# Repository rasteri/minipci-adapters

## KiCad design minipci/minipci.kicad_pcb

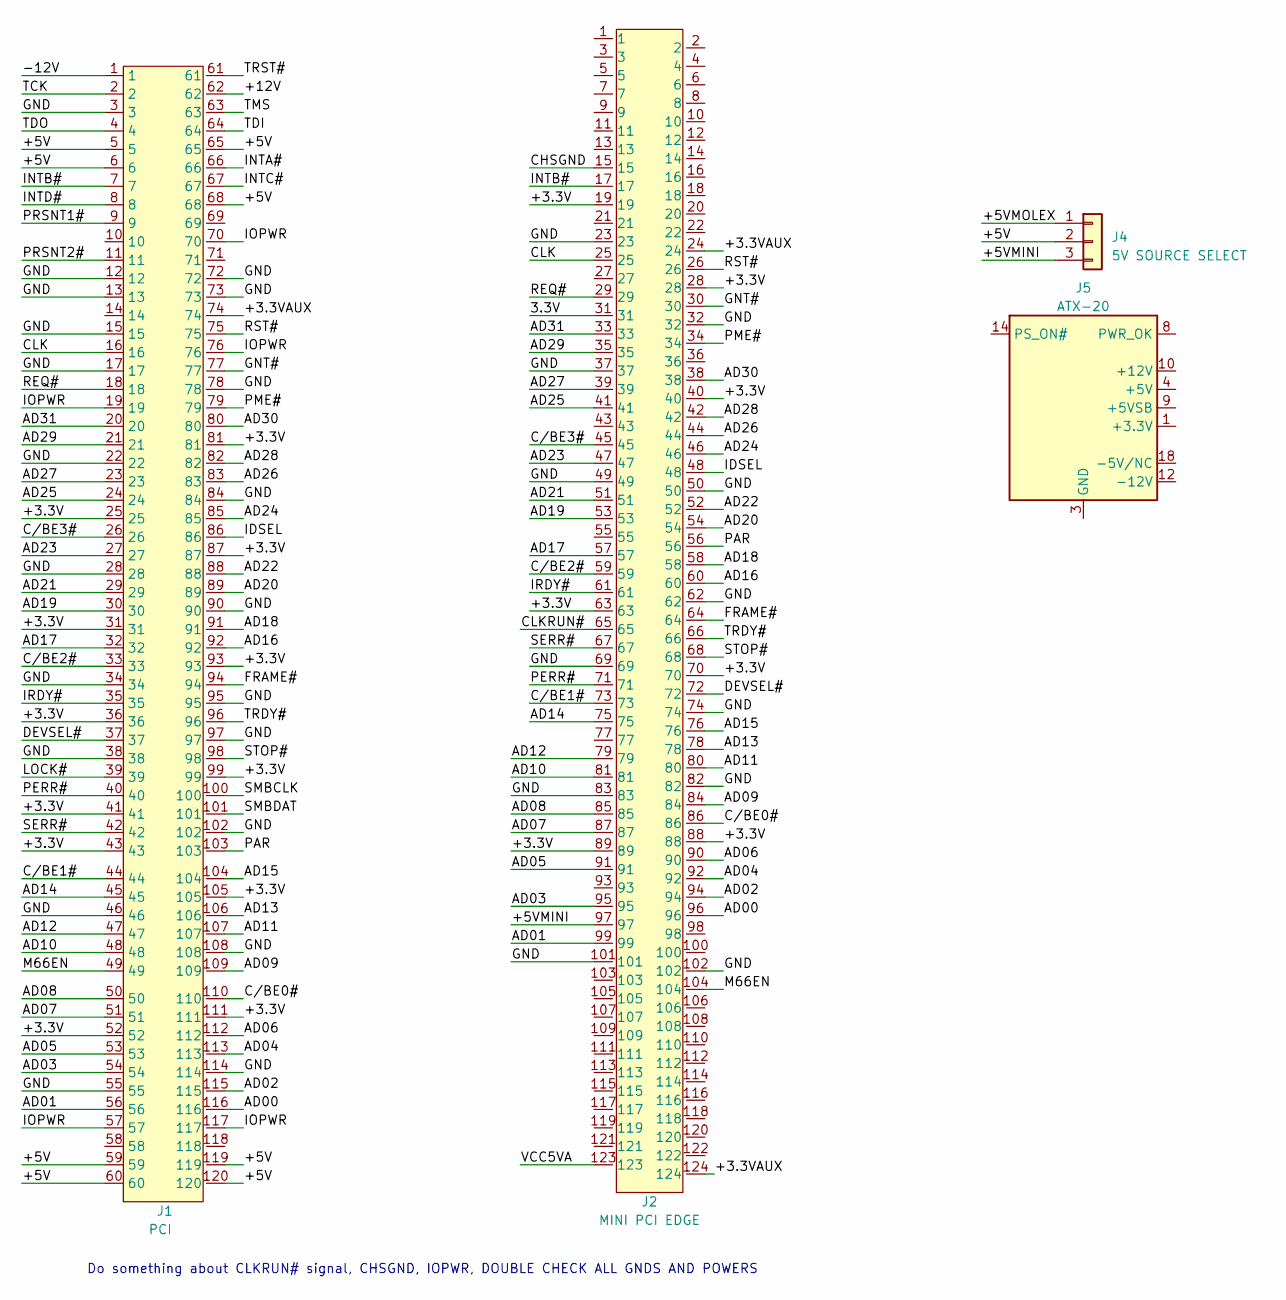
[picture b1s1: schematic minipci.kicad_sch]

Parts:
J1: PCI; 5145154-1
J2: MINI PCI EDGE; minipci
J4: 5V SOURCE SELECT; PinHeader_1x03_P2.54mm_Vertical
J5: ATX-20; Molex_Mini-Fit_Jr_5566-20A_2x10_P4.20mm_Vertical

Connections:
/3.3V: J2.31
/+3.3V: J1.25, J1.31, J1.36, J1.41, J1.43, J1.52, J1.81, J1.87, J1.93, J1.99, J1.105, J1.111, J2.19, J2.28, J2.40, J2.63, J2.70, J2.88, J2.89
/+3.3VAUX: J1.74, J2.24, J2.124
/+5V: J1.5, J1.6, J1.59, J1.60, J1.65, J1.68, J1.119, J1.120, J4.2
/+5VMINI: J2.97, J4.3
/+5VMOLEX: J4.1
/+12V: J1.62
/-12V: J1.1
/AD00: J1.116, J2.96
/AD01: J1.56, J2.99
/AD02: J1.115, J2.94
/AD03: J1.54, J2.95
/AD04: J1.113, J2.92
/AD05: J1.53, J2.91
/AD06: J1.112, J2.90
/AD07: J1.51, J2.87
/AD08: J1.50, J2.85
/AD09: J1.109, J2.84
/AD10: J1.48, J2.81
/AD11: J1.107, J2.80
/AD12: J1.47, J2.79
/AD13: J1.106, J2.78
/AD14: J1.45, J2.75
/AD15: J1.104, J2.76
/AD16: J1.92, J2.60
/AD17: J1.32, J2.57
/AD18: J1.91, J2.58
/AD19: J1.30, J2.53
/AD20: J1.89, J2.54
/AD21: J1.29, J2.51
/AD22: J1.88, J2.52
/AD23: J1.27, J2.47
/AD24: J1.85, J2.46
/AD25: J1.24, J2.41
/AD26: J1.83, J2.44
/AD27: J1.23, J2.39
/AD28: J1.82, J2.42
/AD29: J1.21, J2.35
/AD30: J1.80, J2.38
/AD31: J1.20, J2.33
/CHSGND: J2.15
/CLK: J1.16, J2.25
/CLKRUN#: J2.65
/C/BE0#: J1.110, J2.86
/C/BE1#: J1.44, J2.73
/C/BE2#: J1.33, J2.59
/C/BE3#: J1.26, J2.45
/DEVSEL#: J1.37, J2.72
/FRAME#: J1.94, J2.64
/GND: J1.3, J1.12, J1.13, J1.15, J1.17, J1.22, J1.28, J1.34, J1.38, J1.46, J1.55, J1.72, J1.73, J1.78, J1.84, J1.90, J1.95, J1.97, J1.102, J1.108, J1.114, J2.23, J2.32, J2.37, J2.49, J2.50, J2.62, J2.69, J2.74, J2.82, J2.83, J2.101, J2.102
/GNT#: J1.77, J2.30
/IDSEL: J1.86, J2.48
/INTA#: J1.66
/INTB#: J1.7, J2.17
/INTC#: J1.67
/INTD#: J1.8
/IOPWR: J1.19, J1.57, J1.70, J1.76, J1.117
/IRDY#: J1.35, J2.61
/LOCK#: J1.39
/M66EN: J1.49, J2.104
/PAR: J1.103, J2.56
/PERR#: J1.40, J2.71
/PME#: J1.79, J2.34
/PRSNT1#: J1.9
/PRSNT2#: J1.11
/REQ#: J1.18, J2.29
/RST#: J1.75, J2.26
/SERR#: J1.42, J2.67
/SMBCLK: J1.100
/SMBDAT: J1.101
/STOP#: J1.98, J2.68
/TCK: J1.2
/TDI: J1.64
/TDO: J1.4
/TMS: J1.63
/TRDY#: J1.96, J2.66
/TRST#: J1.61
/VCC5VA: J2.123
unnamed: J5.1 (+3.3V), J5.2 (+3.3V), J5.11 (+3.3V)
unnamed: J5.4 (+5V), J5.6 (+5V), J5.19 (+5V), J5.20 (+5V)
unnamed: J5.3 (GND), J5.5 (GND), J5.7 (GND), J5.13 (GND), J5.15 (GND), J5.16 (GND), J5.17 (GND)

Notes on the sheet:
Do something about CLKRUN# signal, CHSGND, IOPWR, DOUBLE CHECK ALL GNDS AND POWERS

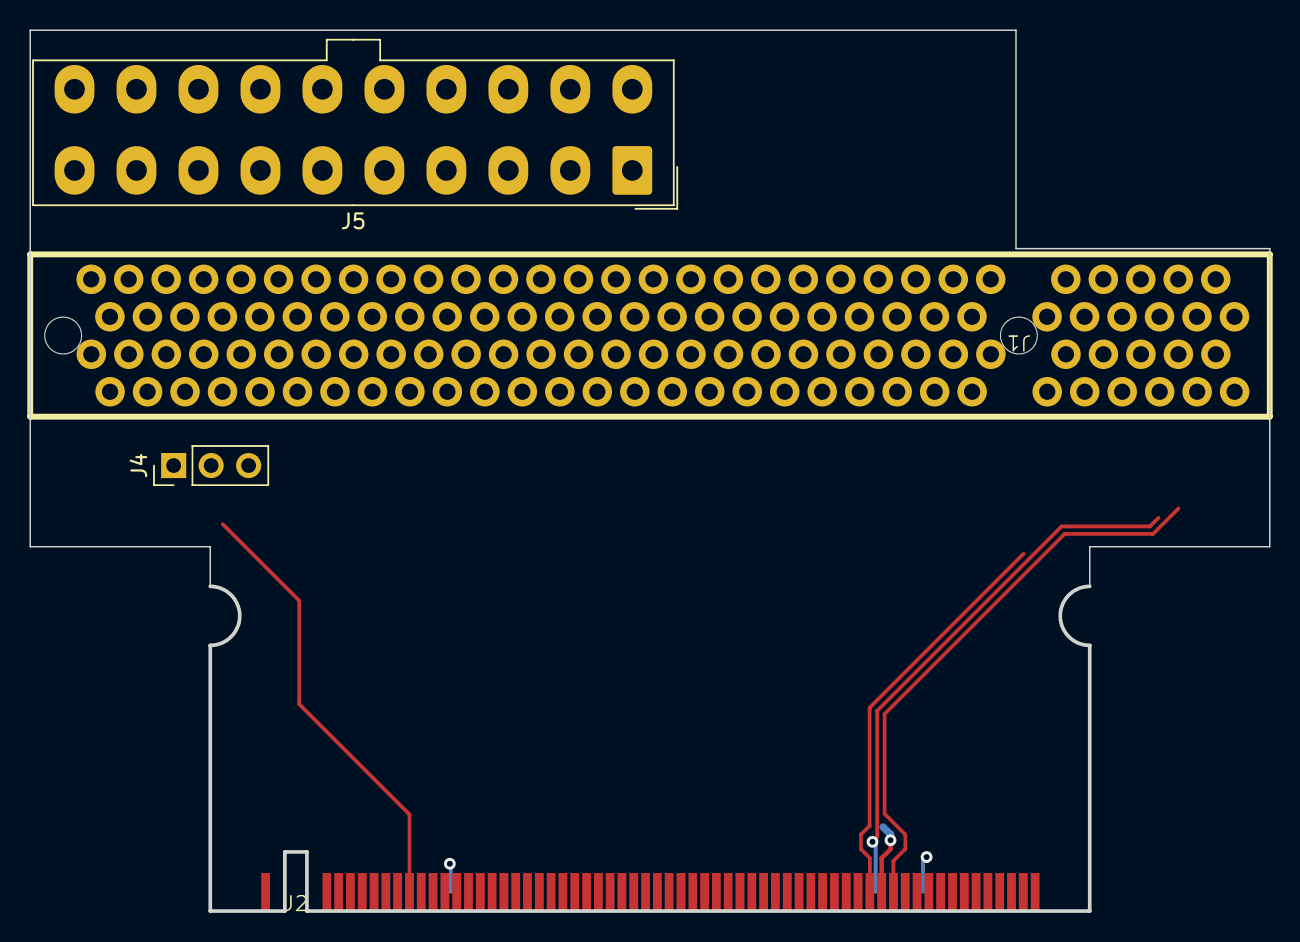
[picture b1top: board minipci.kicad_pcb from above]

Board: 2 copper layers, 83.8 x 59.6 mm, 4 parts (0 on the bottom side), 61 nets.
